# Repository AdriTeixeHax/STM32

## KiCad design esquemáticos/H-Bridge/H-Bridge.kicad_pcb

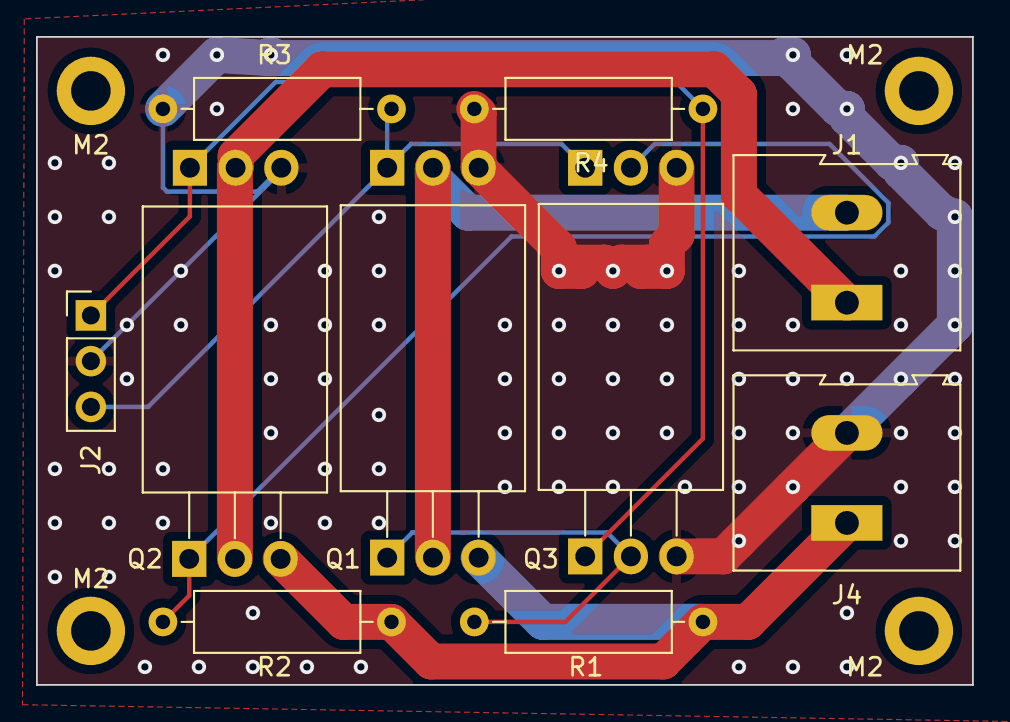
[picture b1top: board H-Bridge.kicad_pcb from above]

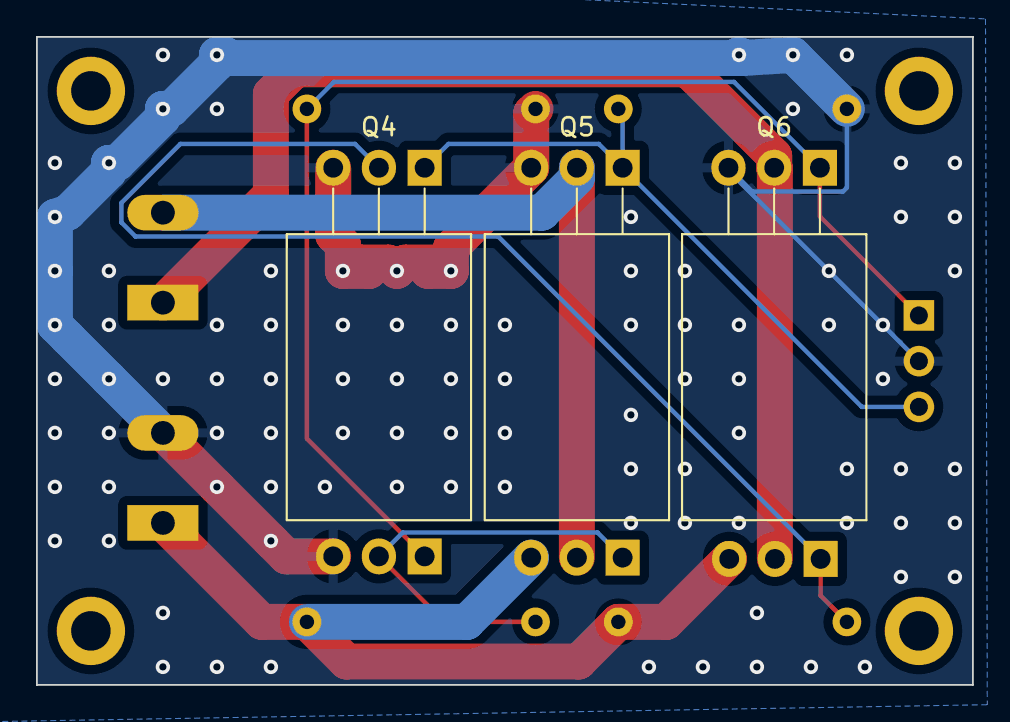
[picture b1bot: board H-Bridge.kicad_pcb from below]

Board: 2 copper layers, 52.0 x 36.0 mm, 17 parts (3 on the bottom side), 8 nets.

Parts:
J1: MOTOR; TerminalBlock_Altech_AK300-2_P5.00mm
J2: Control; PinHeader_1x03_P2.54mm_Vertical
J4: BATTERY; TerminalBlock_Altech_AK300-2_P5.00mm
M2, M2#2, M2#3, M2#4: MountingHole_2.2mm_M2_DIN965_Pad
Q1, Q2: IRF9540N; TO-220-3_Horizontal_TabDown
Q3, Q4, Q5, Q6: IRF510; TO-220-3_Horizontal_TabDown
R1, R2, R3, R4: 10k; R_Axial_DIN0309_L9.0mm_D3.2mm_P12.70mm_Horizontal

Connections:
/A: J2.1, Q3.1 (G), Q6.1 (G), R4.1
/B: J2.3, Q4.1 (G), Q5.1 (G), R3.1
GND: J2.2, J4.2, Q3.3 (S), Q4.3 (S), Q5.3 (S), Q6.3 (S), R3.2, R4.2
unnamed: J1.1, Q2.2 (D), Q6.2 (D)
unnamed: J1.2, Q1.2 (D), Q5.2 (D)
unnamed: Q1.1 (G), Q3.2 (D), R1.2
unnamed: Q2.1 (G), Q4.2 (D), R2.2
VDD: J4.1, Q1.3 (S), Q2.3 (S), R1.1, R2.1

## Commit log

2023-10-18 Added gitignore template for STM32CubeIDE
2023-10-18 Created 3D model for the DC Motor
2023-10-18 Added schematics and arduino code
    Added schematics and arduino code for a basic controller used to test the DC motor
2023-10-27 Añadidas ruedas y soportes para el motor
2023-10-27 Esquemáticos para el puente H creados
2023-10-27 Actualización gitignore
2024-01-04 encoderCodigo
2024-01-08 Añadido el proyecto de la fuente regulada
2024-01-10 Bluetooth funsiona
2024-01-11 Fuente acabada?
2024-01-11 Video
2024-01-11 cosicas
2024-01-11 communications and pwm update
2024-01-11 Proyectofiniquitao
2024-01-11 Vídeos demostrativos
2024-01-11 Video motor
2024-01-11 Puente H actualizado
2024-01-13 Esquemáticos completos
2024-01-14 Moved power suply proyect
2024-01-14 Cambio nombres
2024-01-14 Cambios menores
2024-01-15 Actualizado programa/resolver incompatibilidades
2024-01-15 Cambios en comentarios
2024-04-16 Media movil
2024-04-30 last commit
